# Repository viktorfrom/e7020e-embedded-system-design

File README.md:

# E7020E Embedded System Design
Project designed and written in Rust in conjunction with the E7020E Embedded System Design course at Luleå University of Technology. 

## Project description
The purpose of this project is to create a breathalyzer to estimate the blood alchohol content (BAC) in a person's breath. 
To do this a prototype PCB will be designed connected to an alchohol sensor, a button to start the breathalyzer and a small display to show the alchohol permille detected. Over LoRa this device will also alert a ThinkBoard server that this user's breath contains too much alchohol, i.e. they are about to pass out. 

The goal is to package this is in a simple and safe to use way for users to interact with. The data that is sent to the ThinkBoard server could be seen as sensitive data and would be ideal to encrypt it before transmitting it. 

### Limitations
There is no sure way to calibrate this device as the project team does not have access to a real industry-grade breathalyzer. Thus this device can only very roughly estimate the BAC of a person's breath and SHOULD NOT be trusted in any serious situation where it is critical to know the real BAC.

## Components / shopping list
* [Murata CMWX1ZZABZ-078](https://www.digikey.com/product-detail/en/murata-electronics/CMWX1ZZABZ-078/490-16143-1-ND/6834151)
* [Grove - Alchohol sensor](https://www.elfa.se/en/grove-alcohol-sensor-seeed-studio-101020044/p/30069826)
* [4-pin connector to sensor](https://www.elfa.se/en/grove-universal-pin-connector-seeed-studio-110990030-10pcs-pack/p/30069939)
* [SSD1306 based display](https://cdon.se/hem-tradgard/oled-display-0-96-tum-vit-128x64-pixlar-ssd1306-spi-p50506639)
* [65100516121 USB mini-B](https://www.elfa.se/en/socket-horizontal-mini-usb-smd-wuerth-elektronik-65100516121/p/14257103)
* [Pin headers](https://www.elfa.se/en/wr-phd-straight-male-pcb-header-through-hole-54mm-wuerth-elektronik-61300611121/p/30024526)
* [LM1117IMP-ADJ voltage regulator](https://www.elfa.se/en/ldo-voltage-regulator-800ma-sot-223-texas-instruments-lm1117imp-adj-nopb/p/30019193)
* [2x Electrolytic capacitors 10uF](https://www.elfa.se/en/aluminium-electrolytic-capacitor-10-uf-50-20-vs-panasonic-eee1ha100wr/p/30108011)
* [2x Buttons](https://www.elfa.se/en/print-key-50-ma-12-vdc-te-connectivity-1437565/p/13566525)
* [1x Piezo buzzer](https://www.elfa.se/en/piezo-buzzer-70-db-khz-15-murata-pkm13epyh4000-a0/p/13787082)
* [1x Antenna](https://www.elfa.se/en/micro-coaxial-straight-socket-micro-coaxial-connector-50ohm-6ghz-molex-73412-0110/p/30076410)

## Requirements
* Rustup 1.14.0+
* rustc 1.31.0+ (stable)
* GNU ARM embedded toolchain (check your package manager or manually install it)
* OpenOCD
* Nucleo dev board (in programming mode)
* Breathalyzer PCB

## Setup

### rustc & cargo
Install rustup by following the instructions at https://rustup.rs.

Then install the following tools for rustup and cargo:
```
rustup component add llvm-tools-preview
```
```
rustup target add thumbv6m-none-eabi
```
```
cargo install cargo-binutils
```

### Linux
Below are the absolute minimum packages you will need for Linux. Names might vary depending on your distribution, you might need to install it manually if you can't find it using your distribution's package manager.
```
openocd
arm-none-eabi-gdb
gcc / gcc-c++ (as well as their respective dev packages)
llvm-8.0 (and its dev package)
```

### MacOS
All the tools can be install using Homebrew:
```
brew cask install gcc-arm-embedded

brew install openocd
```
## PCB
The design of the breathalyzer can be found in _/pcbdesign_. It was created and can be opened with KiCad. The program has been written especially for that design.

## Build instructions
First confirm that the correct runner is chosen in _.cargo/config_, as the gdb package name might be different depending on you OS. Then build the project
```
cargo build --features="radio"
```

### Flashing
Connect to the card using the Nucleo F401RE dev board as a programmer with the given configuration
```
openocd -f openocd.cfg
```
Then build the project and flash the card
```
cargo run --features="radio" --release
```

## Authors
* Viktor From - vikfro-6@student.ltu.se - [viktorfrom](https://github.com/viktorfrom)
* Mark Hakansson - marhak-6@student.ltu.se - [markhakansson](https://github.com/markhakansson)
* Kyle Drysdale - kyldry-5@student.ltu.se  - [KyleLouisDrysdale](https://github.com/KyleLouisDrysdale)

## License
Licensed under the MIT license. See [LICENSE](LICENSE) for details.

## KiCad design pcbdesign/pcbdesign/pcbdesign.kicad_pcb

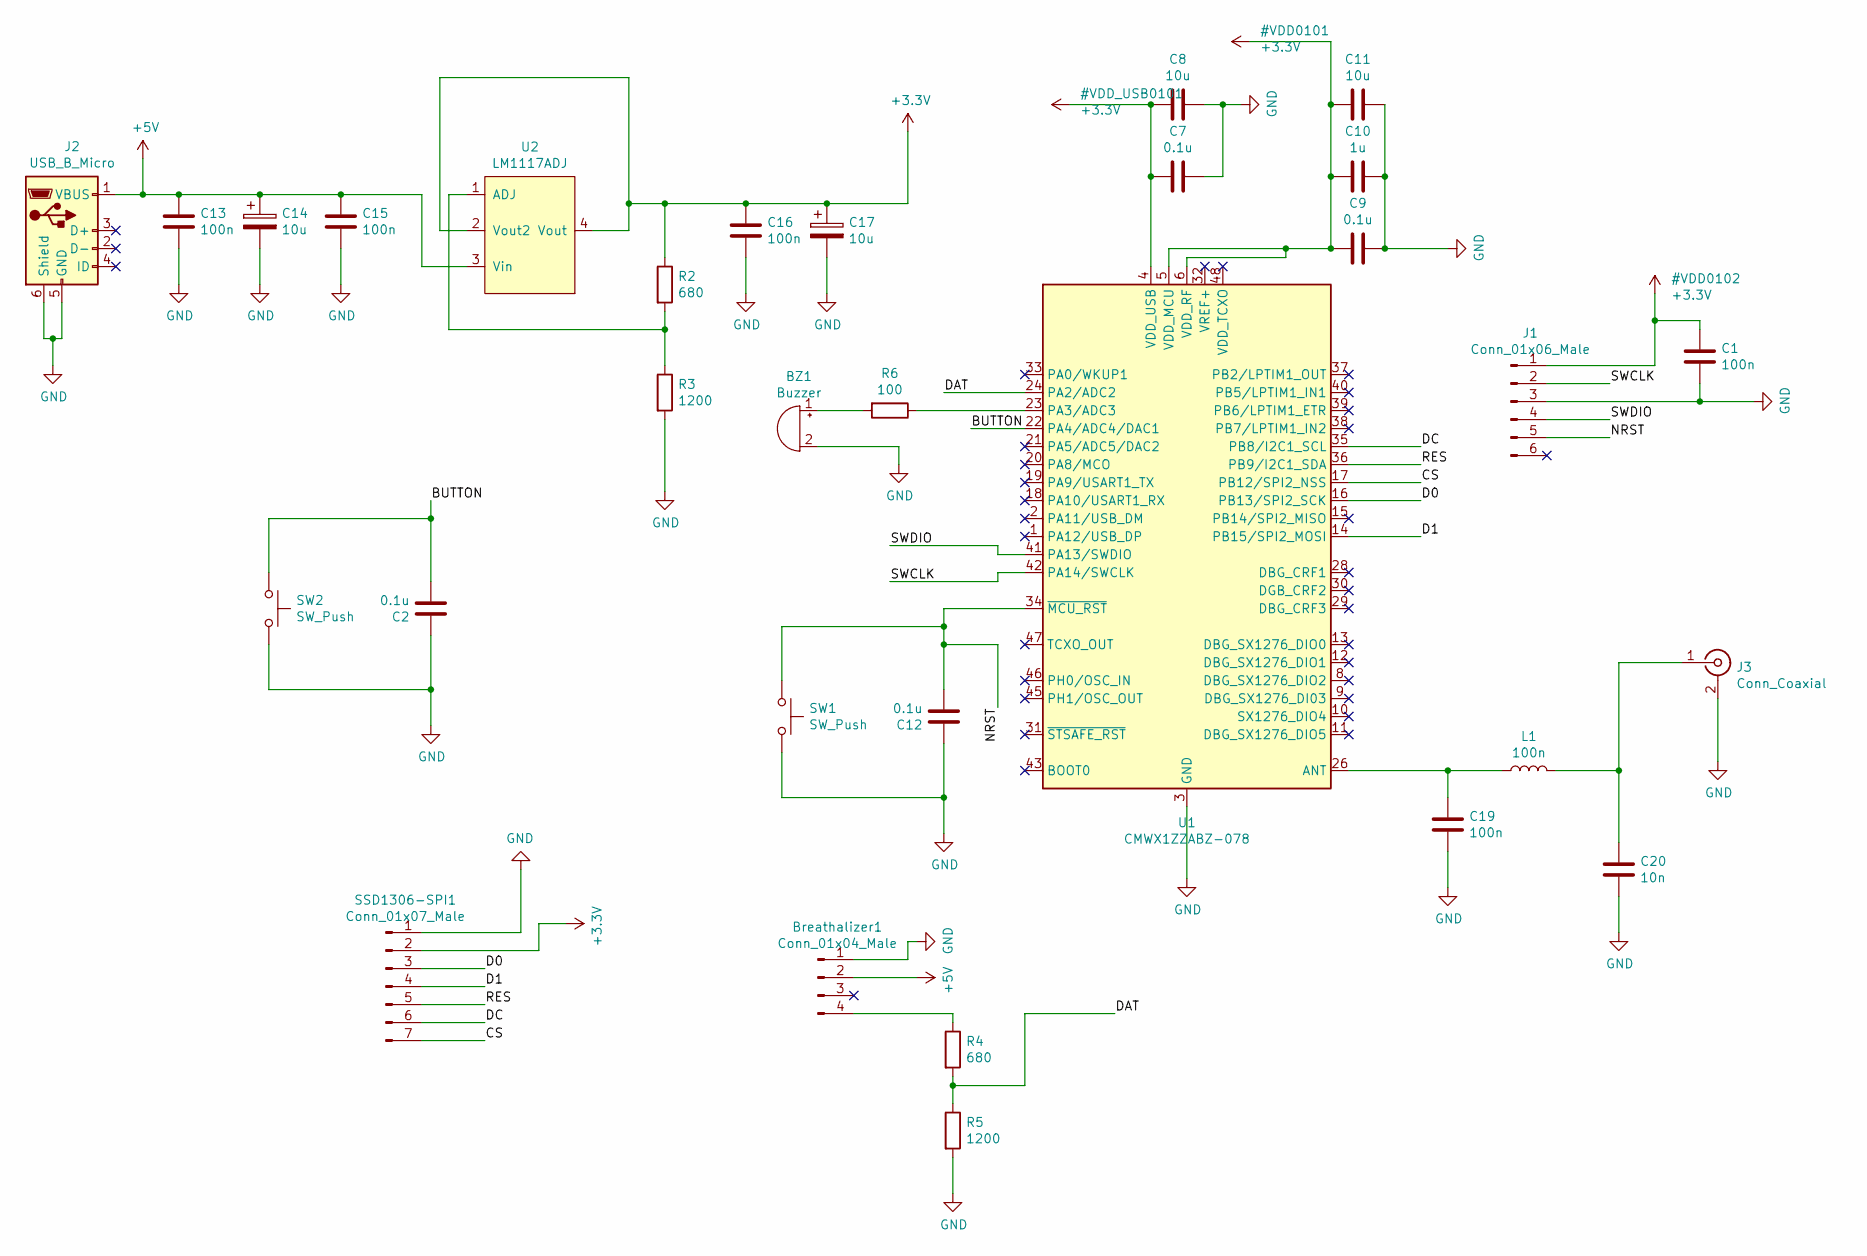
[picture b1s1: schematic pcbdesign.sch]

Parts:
BZ1: Buzzer; PKM13EPYH4000_piezo
Breathalizer1: Conn_01x04_Male; PinHeader_1x04_P2.54mm_Vertical
C1, C13, C15, C16, C19: 100n; C_0805_2012Metric
C2, C7, C9, C12: 0.1u; C_0805_2012Metric
C8, C11: 10u; C_0805_2012Metric
C10: 1u; C_0805_2012Metric
C14, C17: 10u; CP_Elec_5x5.3
C20: 10n; C_0805_2012Metric
J1: Conn_01x06_Male; PinHeader_1x06_P2.54mm_Vertical
J2: USB_B_Micro; USB_Micro-B_Wuerth_629105150521
J3: Conn_Coaxial; U.FL_Molex_MCRF_73412-0110_Vertical
L1: 100n; L_0805_2012Metric
R2, R4: 680; R_0805_2012Metric
R3, R5: 1200; R_0805_2012Metric
R6: 100; R_0805_2012Metric
SSD1306-SPI1: Conn_01x07_Male; PinHeader_1x07_P2.54mm_Vertical
SW1, SW2: SW_Push; SW_Push_1P1T_NO_6x6mm_H9.5mm
U1: CMWX1ZZABZ-078; CMWX1ZZABZ_longer_pads
U2: LM1117ADJ; SOT-223

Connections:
+3V3: C1.1, C7.1, C8.1, C9.1, C10.1, C11.1, C16.1, C17.1, J1.1, R2.1, SSD1306-SPI1.2, U1.4 (VDD_USB), U1.5 (VDD_MCU), U1.6 (VDD_RF), U2.2 (Vout2), U2.4 (Vout)
+5V: Breathalizer1.2, C13.1, C14.1, C15.1, J2.1 (VBUS), U2.3 (Vin)
/BUTTON: C2.2, SW2.1, U1.22 (PA4/ADC4/DAC1)
/CS: SSD1306-SPI1.7, U1.17 (PB12/SPI2_NSS)
/D0: SSD1306-SPI1.3, U1.16 (PB13/SPI2_SCK)
/D1: SSD1306-SPI1.4, U1.14 (PB15/SPI2_MOSI)
/DAT: R4.2, R5.1, U1.24 (PA2/ADC2)
/DC: SSD1306-SPI1.6, U1.35 (PB8/I2C1_SCL)
/NRST: C12.2, J1.5, SW1.1, U1.34 (~MCU_RST)
/RES: SSD1306-SPI1.5, U1.36 (PB9/I2C1_SDA)
/SWCLK: J1.2, U1.42 (PA14/SWCLK)
/SWDIO: J1.4, U1.41 (PA13/SWDIO)
GND: BZ1.2 (+), Breathalizer1.1, C1.2, C2.1, C7.2, C8.2, C9.2, C10.2, C11.2, C12.1, C13.2, C14.2, C15.2, C16.2, C17.2, C19.2, C20.2, J1.3, J2.5 (GND), J2.6 (Shield), J3.2 (Ext), R3.2, R5.2, SSD1306-SPI1.1, SW1.2, SW2.2, U1.3 (GND), U1.7 (GND), U1.25 (GND), U1.27 (GND), U1.44 (GND), U1.49 (GND), U1.50 (GND), U1.51 (GND), U1.52 (GND), U1.53 (GND), U1.54 (GND), U1.55 (GND), U1.56 (GND), U1.57 (GND)
unnamed: BZ1.1 (-), R6.2
unnamed: Breathalizer1.4, R4.1
unnamed: C19.1, L1.1, U1.26 (ANT)
unnamed: C20.1, J3.1 (In), L1.2
unnamed: R2.2, R3.1, U2.1 (ADJ)
unnamed: R6.1, U1.23 (PA3/ADC3)

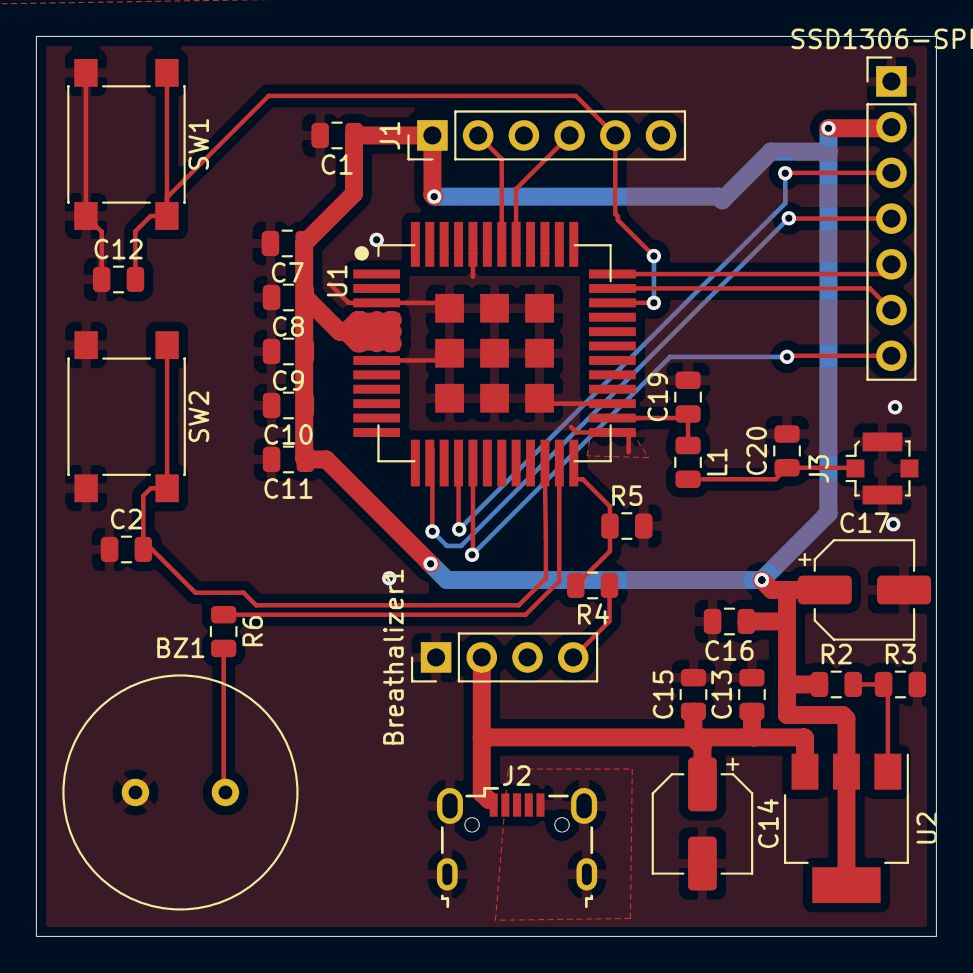
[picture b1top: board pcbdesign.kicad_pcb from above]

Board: 2 copper layers, 50.0 x 50.0 mm, 31 parts (0 on the bottom side), 19 nets.

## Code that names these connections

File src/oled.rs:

use ssd1306::{interface::SpiInterface, prelude::*, Builder};
extern crate panic_semihosting;

use stm32l0xx_hal::{
    delay::Delay,
    gpio::{
        gpiob::{PB13, PB15, PB8, PB9},
        *,
    },
    pac::SPI2,
    spi::{NoMiso, Spi},
};

use embedded_graphics::{
    fonts::{Font6x12, Font8x16, Text},
    pixelcolor::BinaryColor,
    prelude::*,
    primitives::{Circle, Rectangle},
    style::{PrimitiveStyleBuilder, TextStyle},
};

pub struct Oled {
    pub pb9: PB9<Output<PushPull>>,
    pub delay: Delay,
    pub disp: GraphicsMode<
        SpiInterface<
            Spi<SPI2, (PB13<Input<Floating>>, NoMiso, PB15<Input<Floating>>)>,
            PB8<Output<PushPull>>,
        >,
    >,
    pub style1:
        embedded_graphics::style::PrimitiveStyle<embedded_graphics::pixelcolor::BinaryColor>,
    pub style2:
        embedded_graphics::style::PrimitiveStyle<embedded_graphics::pixelcolor::BinaryColor>,
    pub state: bool,
}

impl Oled {
    pub fn new(
        spi: Spi<SPI2, (PB13<Input<Floating>>, NoMiso, PB15<Input<Floating>>)>,
        pb8: PB8<Input<Floating>>,
        pb9: PB9<Input<Floating>>,
        delay: Delay,
    ) -> Oled {
        Oled {
            pb9: pb9.into_push_pull_output(),
            disp: Builder::new()
                .connect_spi(spi, pb8.into_push_pull_output())
                .into(),
            delay: delay,
            style1: PrimitiveStyleBuilder::new()
                .stroke_color(BinaryColor::On)
                .stroke_width(2)
                .fill_color(BinaryColor::On)
                .build(),
            style2: PrimitiveStyleBuilder::new()
                .stroke_color(BinaryColor::On)
                .stroke_width(2)
                .fill_color(BinaryColor::Off)
                .build(),
            state: false,
        }
    }

    pub fn on(&mut self, message: &str) {
        let res = &mut self.pb9;

        self.disp.reset(res, &mut self.delay).unwrap();
        self.disp.init().unwrap();

        self.disp.clear();

        Circle::new(Point::new(27, 23), 5)
            .into_styled(self.style2)
            .draw(&mut self.disp);

        Rectangle::new(Point::new(10, 20), Point::new(25, 35))
            .into_styled(self.style1)
            .draw(&mut self.disp);

        Rectangle::new(Point::new(10, 15), Point::new(25, 20))
            .into_styled(self.style2)
            .draw(&mut self.disp);

        let t1 = Text::new("Breathalyzer", Point::new(40, 16))
            .into_styled(TextStyle::new(Font6x12, BinaryColor::On));

        let t2 = Text::new(message, Point::new(40, 35))
            .into_styled(TextStyle::new(Font8x16, BinaryColor::On));

        t1.draw(&mut self.disp);
        t2.draw(&mut self.disp);

        self.disp.flush().unwrap();

        self.state = true;
    }

    pub fn off(&mut self) {
        let res = &mut self.pb9;

        self.disp.reset(res, &mut self.delay).unwrap();
        self.disp.init().unwrap();

        self.disp.clear();

        // clear display

        self.disp.flush().unwrap();

        self.state = false;
    }
}

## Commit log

2020-01-20 Create LICENSE
2020-01-20 Init commit
2020-02-03 Add pcbdesign
2020-02-03 Update pcbdesign
2020-02-03 Add Murata lib
2020-02-06 Add pull-up resistor to CS pin on SPI connector
2020-02-10 Place components on PCB
2020-02-11 Finish copper routing
2020-02-12 Finish review of board. Add text and logo to PCB
2020-02-13 Add gerber files
2020-02-17 Merge
2020-02-17 Add configs for running the debugging tools.
2020-02-28 Add stm32l0.cfg
2020-03-02 Update project to use stm32l0 and RTFM
2020-03-03 Update memory.x to use STM32l0x2 memory values
2020-03-04 Update build for Cortex M0
2020-03-04 Add longfi to project
2020-03-04 Remove ITM from gdb file as there is no support for it on the STM32L0X2
2020-03-04 Add dual bank config for openocd
2020-03-04 Change from RTFM v0.4 to v0.5
2020-03-09 Remove Aron's code in main for now
2020-03-09 Comment out longfi dependencies from Cargo.toml
2020-03-09 Add ccynt and monotonic to project
2020-03-10 Initialize buzzer example
2020-03-10 Add oled.rs
2020-03-11 Add dvd.bmp
2020-03-11 Update crates
2020-03-11 Finish buzzer
2020-03-13 Remove unused resources in main
2020-03-13 Add SPI2 connection to oled example
2020-03-13 Add oled example
2020-03-15 Oled example now displays a square box!
2020-03-16 Update oled
2020-03-16 Update cargo toml and lock name
2020-03-16 Add example for alcohol sensor
2020-03-16 Finish alcohol sensor example
2020-03-17 Add breathalyzer as a module to project
2020-03-17 Add oled2
2020-03-17 Update cargo toml, lock
2020-03-18 Update oled2
2020-03-18 Update dependencies correct combination
2020-03-18 Add buzzer as module
2020-03-18 Add tinybmp
2020-03-18 Cargo fmt
2020-03-20 Update font size
2020-03-20 Update buzzer example with intervals between beeps
2020-03-20 Update and add buzzer to main project
2020-03-22 Update the buzzer module to be more intuitive. Buzzer and sensor can run simultanously
2020-03-22 Update dependencies
2020-03-22 Update formatting
2020-03-22 Add mod oled to main
2020-03-23 Format with cargo fmt
2020-03-24 Add oled on button press
2020-03-24 Add off function
2020-03-27 Update Cargo.toml with radio features
2020-03-27 Add radio examples
2020-03-27 Add WIP radio features to the project
2020-03-31 Update warm up procedure
2020-03-31 Update radio exampl
2020-03-31 Remove radio.rs from project. Could not abstract the code as I wanted
2020-04-01 Update PCB schematic to include the missing wires
2020-04-01 Add wire for LoRa crystal, annotate forgotten resistor
2020-04-01 Add more BAC levels in breathalyzer
2020-04-01 Add send message over radio for the project
2020-04-02 Update README.md
    Add build instructions to readme
2020-04-02 Update README.md
    Fix spelling mistakes...
2020-04-02 Fix buzzer bug where the button press would be ignored sometimes
2020-04-02 Update gdb script to not break at beginning of code
2020-04-02 Send radio message now takes BAC enum as input
2020-04-02 Dervice debug on BAC enum in breathalyzer
2020-04-02 Remove use of pressing "c" on boot
2020-04-02 Connect sensor to OLED
2020-04-02 Update toml
2020-04-02 Change panic handler in project
2020-04-03 Add 3 sec delay when running breathalyzer
2020-04-03 Final STL files for breathalyzer shell.
2020-04-07 Fix task priorities. It is no longe possible to spam multiple tasks while breathalyzer is running
